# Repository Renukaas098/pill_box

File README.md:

# pill_box
ai integrated pillbox

### create ENV
-   py -3.11 -m venv venv

### activate for windows only -->
-   venv\Scripts\activate

### install requirements.txt
-   pip install -r requirement.txt

# uvx commands -->

uvx ruff check .
uvx ruff format .
uvx ruff check . --select I --fix

# First run detection

python main.py detect

# second embed

python main.py embed

# testing with image path

python main.py recognize --image "src\dataset\Alvaro Morte\Alvaro Morte1_152.jpg"

# Testing with webcam

python main.py webcam

DELETE /user/{name}
POST   /reload_embeddings
GET    /detection_log
GET    /model_status

/device/register
/device/list
/device/wifi-scan
/device/wifi-setup
/device/action

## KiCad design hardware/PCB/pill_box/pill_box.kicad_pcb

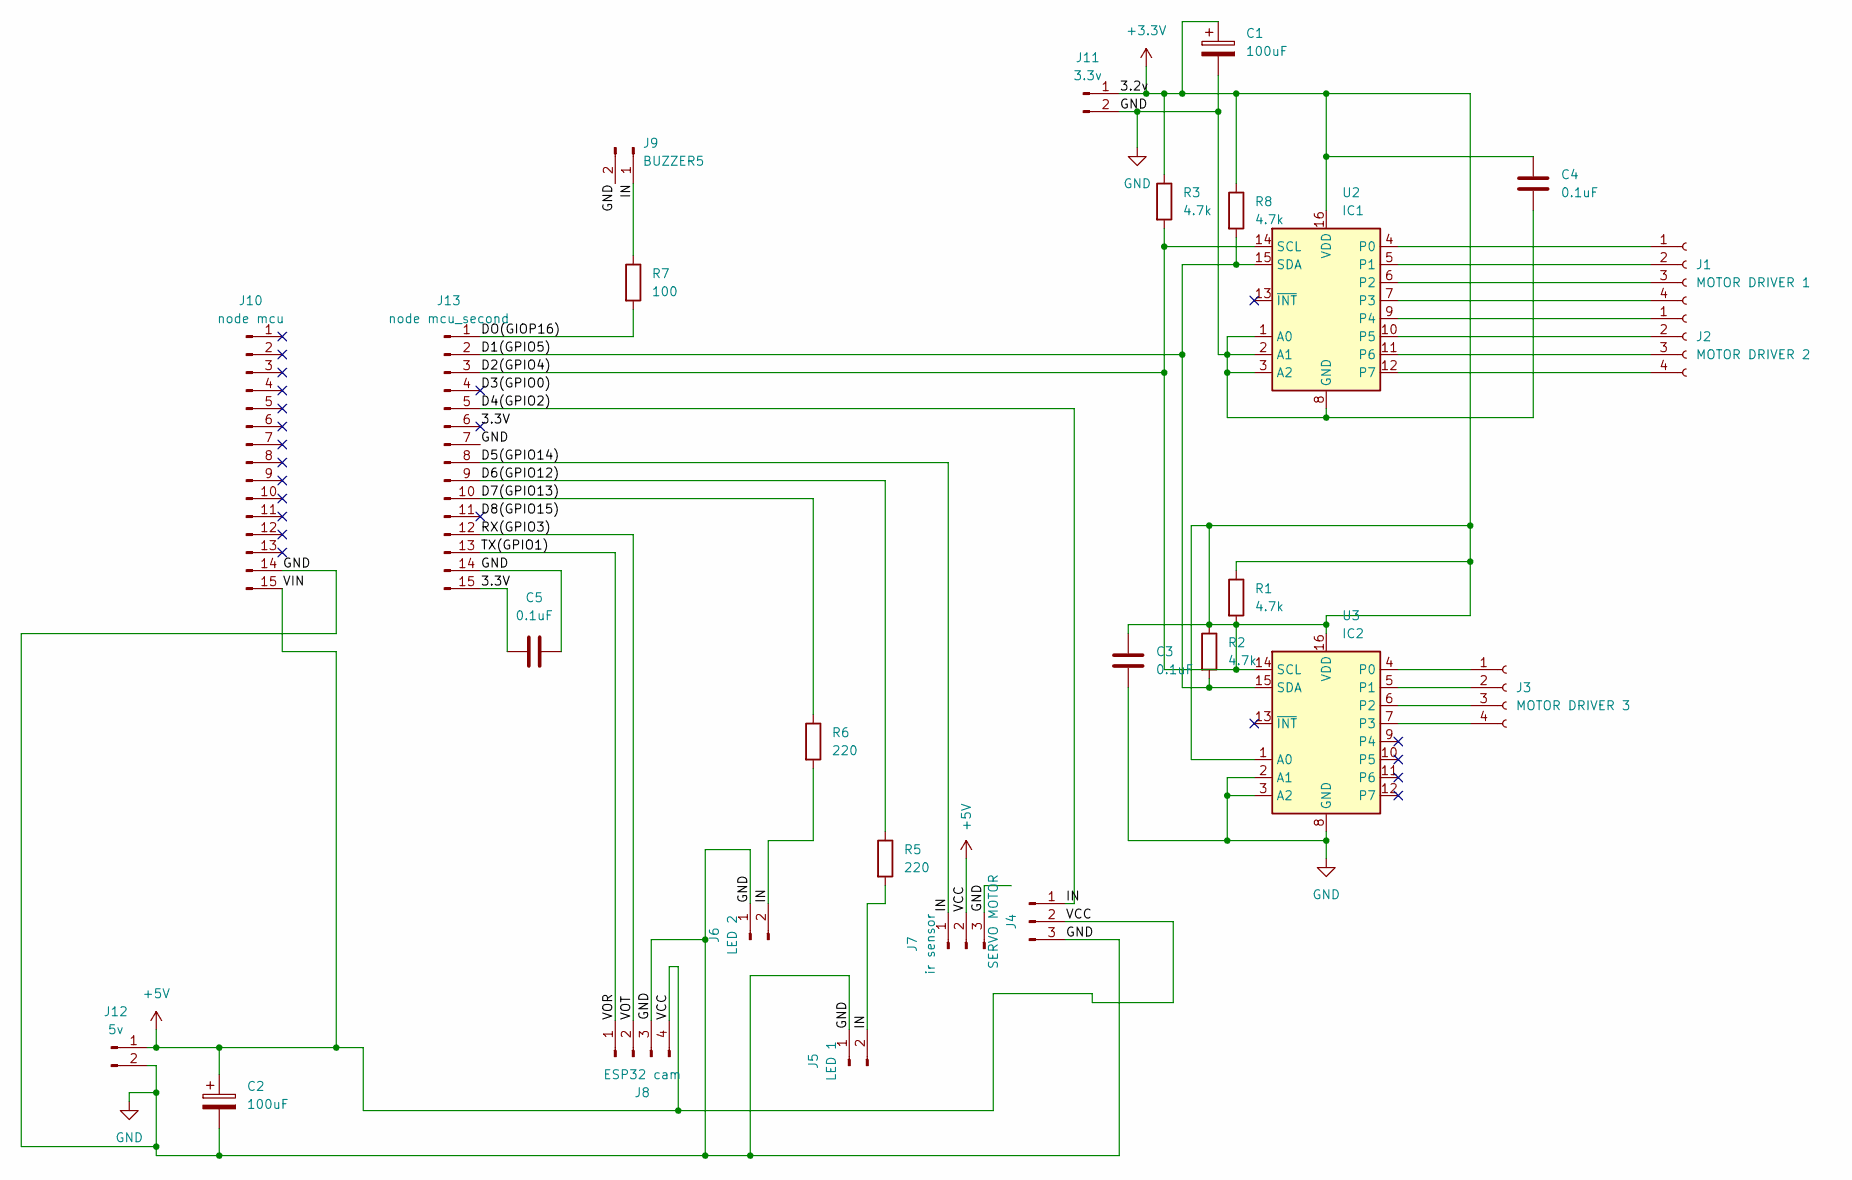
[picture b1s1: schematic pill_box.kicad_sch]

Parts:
C1, C2: 100uF; CP_Radial_D8.0mm_P3.50mm
C3, C4, C5: 0.1uF; C_Disc_D5.0mm_W2.5mm_P2.50mm
J1: MOTOR DRIVER 1; PinHeader_1x04_P2.54mm_Vertical
J2: MOTOR DRIVER 2; PinHeader_1x04_P2.54mm_Vertical
J3: MOTOR DRIVER 3; PinHeader_1x04_P2.54mm_Vertical
J4: SERVO MOTOR; PinHeader_1x03_P2.54mm_Vertical
J5: LED 1; PinHeader_1x02_P2.54mm_Vertical
J6: LED 2; PinHeader_1x02_P2.54mm_Vertical
J7: ir sensor; PinHeader_1x03_P2.54mm_Vertical
J8: ESP32 cam; PinHeader_1x04_P2.54mm_Vertical
J9: BUZZER5; PinHeader_1x02_P2.54mm_Vertical
J10: node mcu; PinHeader_1x15_P2.54mm_Vertical
J11: 3.3v; PinHeader_1x02_P2.54mm_Vertical
J12: 5v; PinHeader_1x02_P2.54mm_Vertical
J13: node mcu_second; PinHeader_1x15_P2.54mm_Vertical
R1, R2, R3, R8: 4.7k; R_Axial_DIN0207_L6.3mm_D2.5mm_P7.62mm_Horizontal
R5, R6: 220; R_Axial_DIN0207_L6.3mm_D2.5mm_P7.62mm_Horizontal
R7: 100; R_Axial_DIN0207_L6.3mm_D2.5mm_P7.62mm_Horizontal
U2: IC1; CERDIP-16_W7.62mm_SideBrazed
U3: IC2; CERDIP-16_W7.62mm_SideBrazed

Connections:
+3.3V: C1.1, C3.1, C4.1, J11.1, J13.3, R1.1, R1.2, R2.1, R3.1, R3.2, R8.1, U2.14 (SCL), U2.16 (VDD), U3.1 (A0), U3.14 (SCL), U3.16 (VDD)
+5V: C2.1, J4.2, J7.2, J8.4, J10.15, J12.1
/3.3V: C5.1, J13.6, J13.15
/D1(GPIO5): J13.2, R2.2, R8.2, U2.15 (SDA), U3.15 (SDA)
/D3(GPIO0): J13.4
/D4(GPIO2): J4.1, J5.2, J6.2, J7.1, J9.1, J13.5, J13.8, R5.2, R6.2, R7.1
/D6(GPIO12): J13.9, R5.1
/D7(GPIO13): J13.10, R6.1
/D8(GPIO15): J13.11
/DO(GIOP16): J13.1, R7.2
/RX(GPIO3): J8.2, J13.12
/TX(GPIO1): J8.1, J13.13
GND: C1.2, C2.2, C3.2, C4.2, C5.2, J4.3, J5.1, J6.1, J7.3, J8.3, J9.2, J10.14, J11.2, J12.2, J13.7, J13.14, U2.1 (A0), U2.2 (A1), U2.3 (A2), U2.8 (GND), U3.2 (A1), U3.3 (A2), U3.8 (GND)
unnamed: J1.1, U2.4 (P0)
unnamed: J1.2, U2.5 (P1)
unnamed: J1.3, U2.6 (P2)
unnamed: J1.4, U2.7 (P3)
unnamed: J2.1, U2.9 (P4)
unnamed: J2.2, U2.10 (P5)
unnamed: J2.3, U2.11 (P6)
unnamed: J2.4, U2.12 (P7)
unnamed: J3.1, U3.4 (P0)
unnamed: J3.2, U3.5 (P1)
unnamed: J3.3, U3.6 (P2)
unnamed: J3.4, U3.7 (P3)

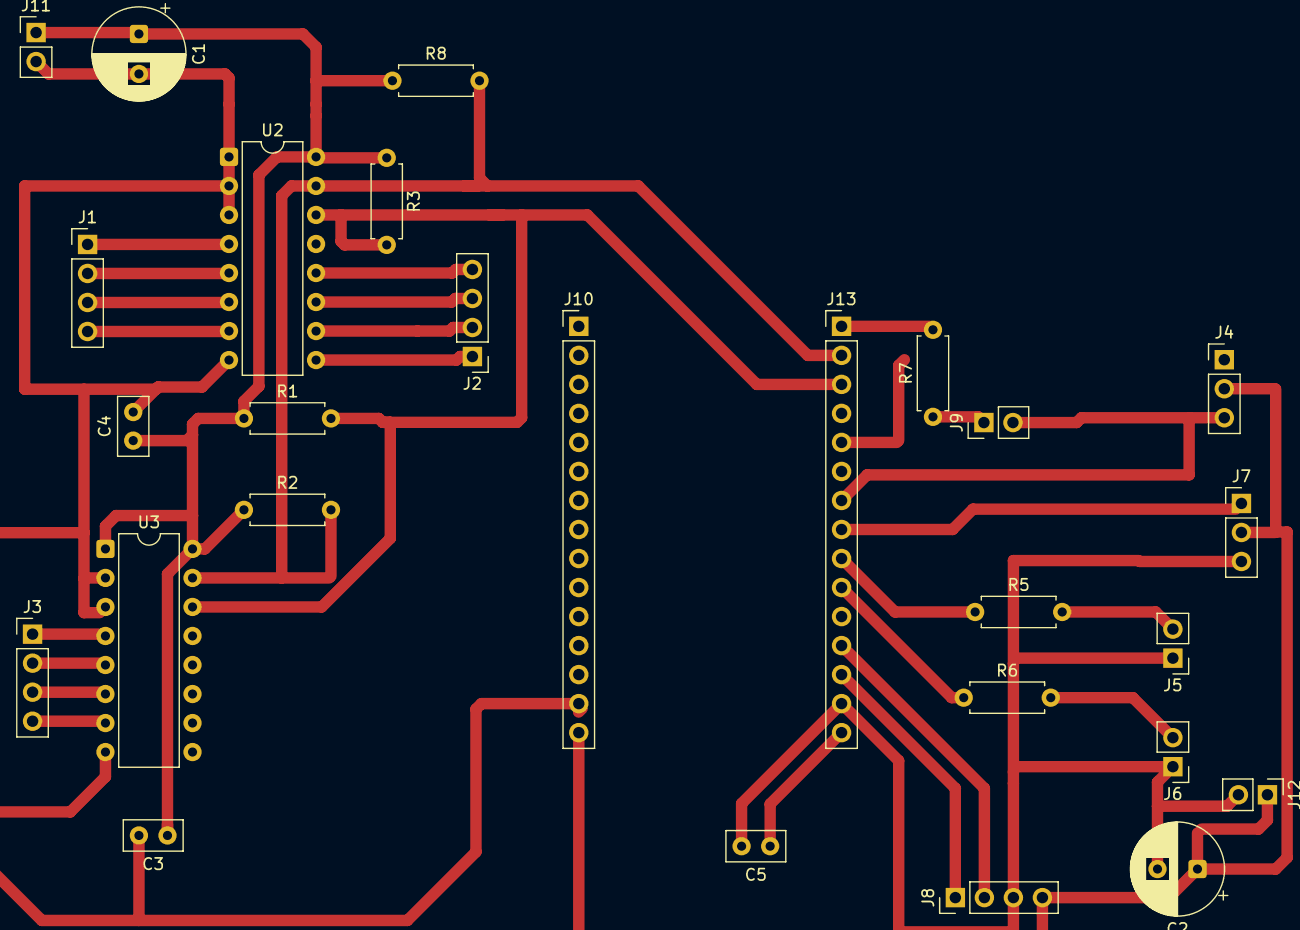
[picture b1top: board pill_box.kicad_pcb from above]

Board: 2 copper layers, 27 parts (0 on the bottom side), 23 nets.

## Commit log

2026-02-12 my testing code
2026-02-12 branch testing
2026-02-12 requirements
2026-02-12 create env setup
2026-02-12 added install command
2026-02-12 error in command
2026-02-12 corrected the format
2026-02-12 my intro commit
2026-02-12 intro
2026-02-12 code setup
2026-02-12 readme
2026-02-12 face recognition final setup
2026-02-12 yolo face detection code
2026-02-12 ssl permission
2026-02-12 model cache
2026-02-12 yolo model
2026-02-12 testing
2026-02-12 added
2026-02-12 added ignore
2026-02-13 integrated recognition
2026-02-13 changed
2026-03-09 api changes code new integration with ui
2026-03-09 new code with hardware
2026-03-11 NEW CODE
2026-03-11 MINOR CHANGE
2026-03-11 ALL DONE
2026-03-11 solved the issue
2026-03-24 HARDWARE
2026-03-25 made some wiring changes
2026-03-25 capacitor
2026-03-25 pcb trace width increased
2026-03-26 checking commit
2026-03-26 revert commit
2026-03-26 added changes
